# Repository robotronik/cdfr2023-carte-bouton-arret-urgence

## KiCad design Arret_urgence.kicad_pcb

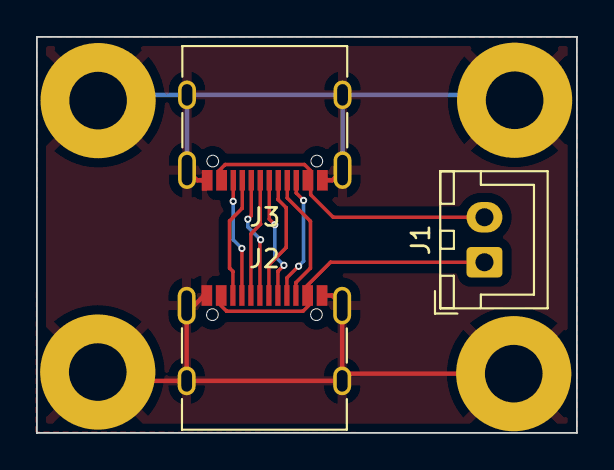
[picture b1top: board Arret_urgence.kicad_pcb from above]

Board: 2 copper layers, 30.0 x 22.0 mm, 3 parts (0 on the bottom side), 11 nets.

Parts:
J1: Conn_01x02; JST_XH_B2B-XH-A_1x02_P2.50mm_Vertical
J2, J3: USB_C_Receptacle_USB2.0; USB_C_Receptacle_XKB_U262-16XN-4BVC11

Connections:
GND: J2.A1 (GND), J2.A12 (GND), J2.B1 (GND), J2.B12 (GND), J2.S1 (SHIELD), J3.A1 (GND), J3.A12 (GND), J3.B1 (GND), J3.B12 (GND), J3.S1 (SHIELD)
unnamed: J1.2, J3.A4 (VBUS), J3.A9 (VBUS), J3.B4 (VBUS), J3.B9 (VBUS)
unnamed: J1.1, J2.A4 (VBUS), J2.A9 (VBUS), J2.B4 (VBUS), J2.B9 (VBUS)
unnamed: J2.A5 (CC1), J3.B5 (CC2)
unnamed: J2.A6 (D+), J3.B6 (D+)
unnamed: J2.A7 (D-), J3.B7 (D-)
unnamed: J2.A8 (SBU1), J3.B8 (SBU2)
unnamed: J2.B5 (CC2), J3.A5 (CC1)
unnamed: J2.B6 (D+), J3.A6 (D+)
unnamed: J2.B7 (D-), J3.A7 (D-)
unnamed: J2.B8 (SBU2), J3.A8 (SBU1)

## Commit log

2023-02-02 initial import with usb on each face
2023-02-02 modif schematic
2023-04-28 modif
